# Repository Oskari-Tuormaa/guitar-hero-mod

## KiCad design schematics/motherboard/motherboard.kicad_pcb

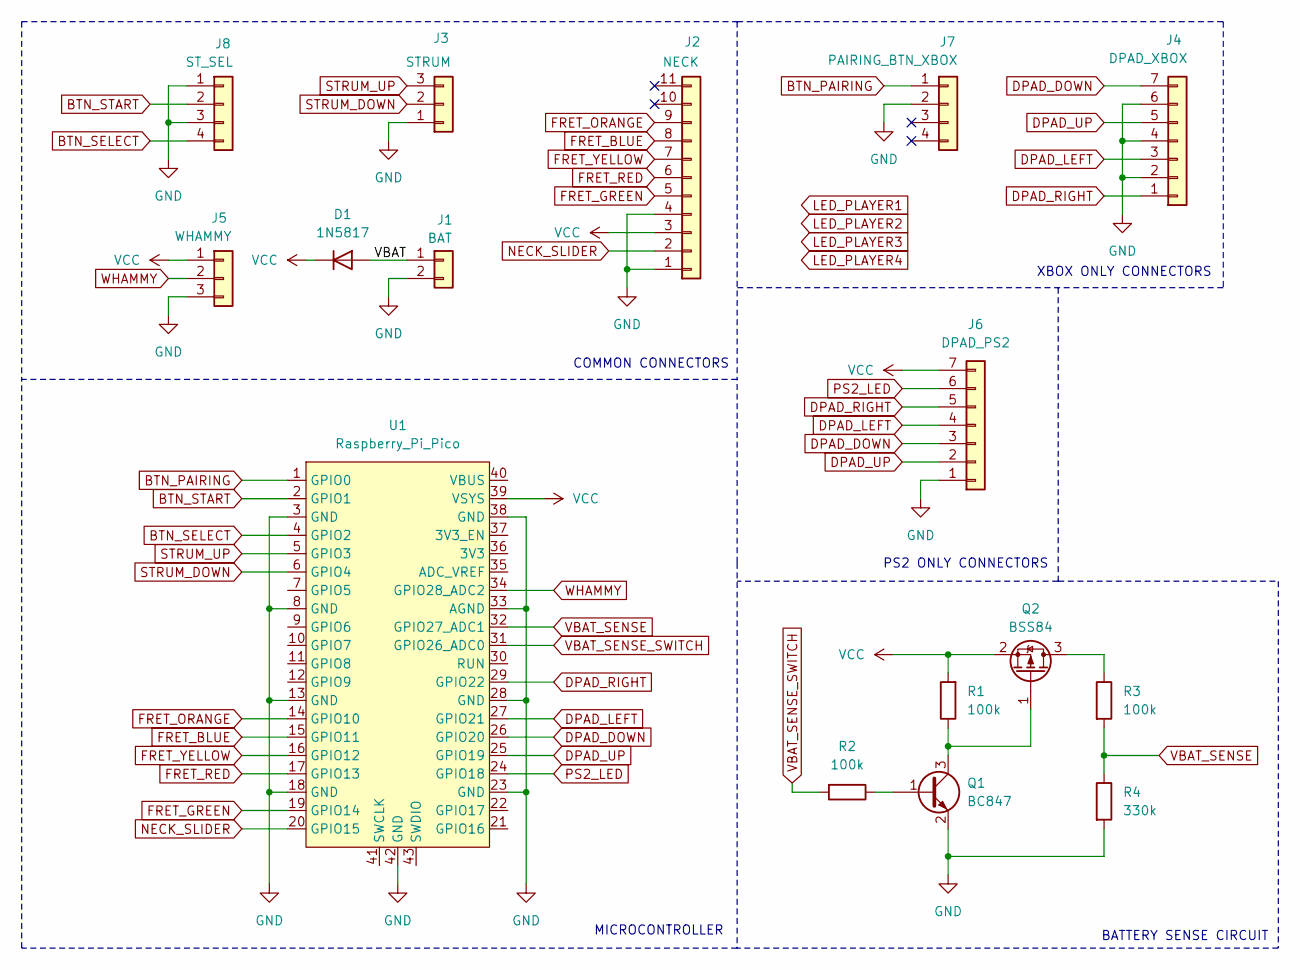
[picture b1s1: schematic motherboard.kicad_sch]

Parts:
D1: 1N5817; D_DO-41_SOD81_P7.62mm_Horizontal
J1: BAT; PinHeader_1x02_P2.00mm_Vertical
J2: NECK; PinHeader_1x11_P2.00mm_Vertical
J3: STRUM; PinHeader_1x03_P2.00mm_Vertical
J4: DPAD_XBOX; PinHeader_1x07_P2.00mm_Vertical
J5: WHAMMY; PinHeader_1x03_P2.00mm_Vertical
J6: DPAD_PS2; PinHeader_1x07_P2.00mm_Vertical
J7: PAIRING_BTN_XBOX; PinHeader_1x04_P2.00mm_Vertical
J8: ST_SEL; PinHeader_1x04_P2.00mm_Vertical
Q1: BC847; SOT-23
Q2: BSS84; SOT-23
R1, R2, R3: 100k; R_1206_3216Metric
R4: 330k; R_1206_3216Metric
U1: Raspberry_Pi_Pico

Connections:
/VBAT: D1.2 (A), J1.1
BTN_PAIRING: J7.1, U1.1 (GPIO0)
BTN_SELECT: J8.4, U1.4 (GPIO2)
BTN_START: J8.2, U1.2 (GPIO1)
DPAD_DOWN: J4.7, J6.3, U1.26 (GPIO20)
DPAD_LEFT: J4.3, J6.4, U1.27 (GPIO21)
DPAD_RIGHT: J4.1, J6.5, U1.29 (GPIO22)
DPAD_UP: J4.5, J6.2, U1.25 (GPIO19)
FRET_BLUE: J2.8, U1.15 (GPIO11)
FRET_GREEN: J2.5, U1.19 (GPIO14)
FRET_ORANGE: J2.9, U1.14 (GPIO10)
FRET_RED: J2.6, U1.17 (GPIO13)
FRET_YELLOW: J2.7, U1.16 (GPIO12)
GND: J1.2, J2.1, J2.4, J3.1, J4.2, J4.4, J4.6, J5.3, J6.1, J7.2, J8.1, J8.3, Q1.2 (E), R4.2, U1.3 (GND), U1.8 (GND), U1.13 (GND), U1.18 (GND), U1.23 (GND), U1.28 (GND), U1.33 (AGND), U1.38 (GND), U1.42 (GND)
NECK_SLIDER: J2.2, U1.20 (GPIO15)
unnamed: Q1.1 (B), R2.1
unnamed: Q1.3 (C), Q2.1 (G), R1.1
unnamed: Q2.3 (D), R3.1
PS2_LED: J6.6, U1.24 (GPIO18)
STRUM_DOWN: J3.2, U1.6 (GPIO4)
STRUM_UP: J3.3, U1.5 (GPIO3)
VBAT_SENSE: R3.2, R4.1, U1.32 (GPIO27_ADC1)
VBAT_SENSE_SWITCH: R2.2, U1.31 (GPIO26_ADC0)
VCC: D1.1 (K), J2.3, J5.1, J6.7, Q2.2 (S), R1.2, U1.39 (VSYS)
WHAMMY: J5.2, U1.34 (GPIO28_ADC2)

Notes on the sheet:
BATTERY SENSE CIRCUIT
COMMON CONNECTORS
MICROCONTROLLER
XBOX ONLY CONNECTORS
PS2 ONLY CONNECTORS

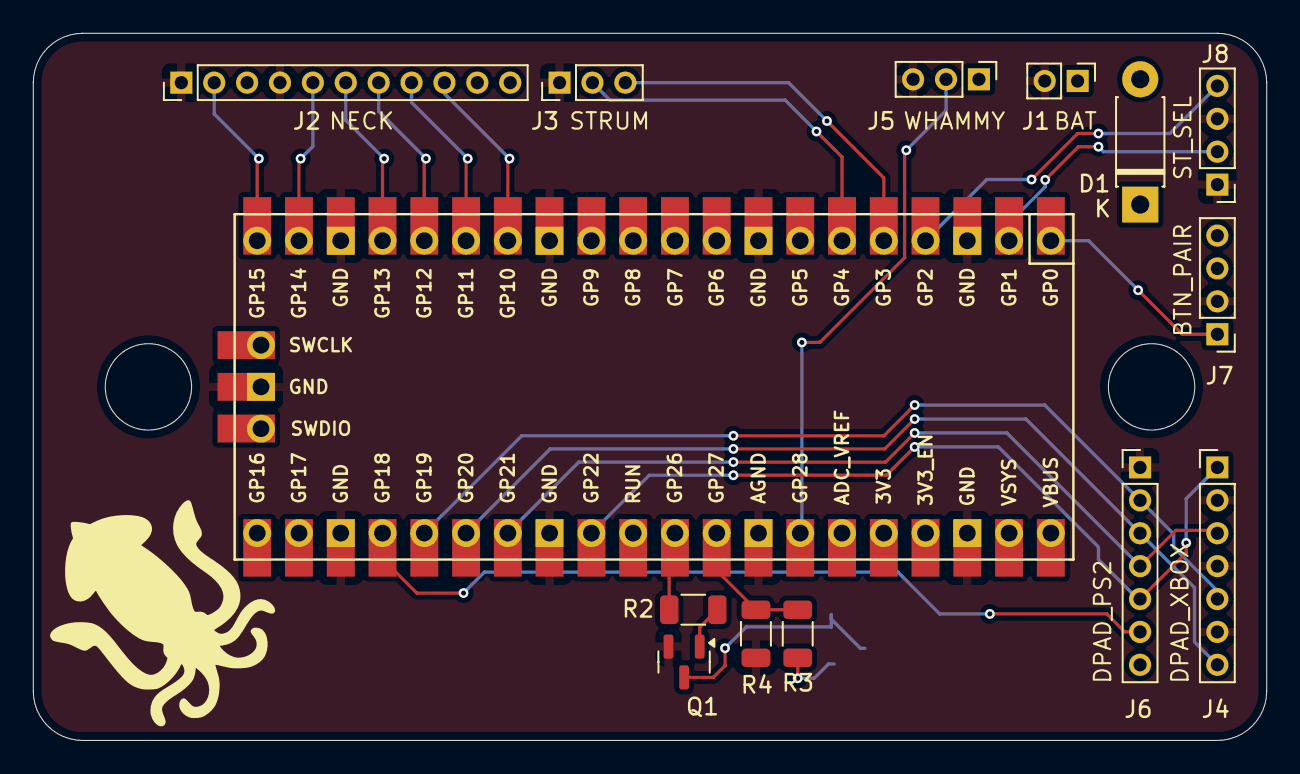
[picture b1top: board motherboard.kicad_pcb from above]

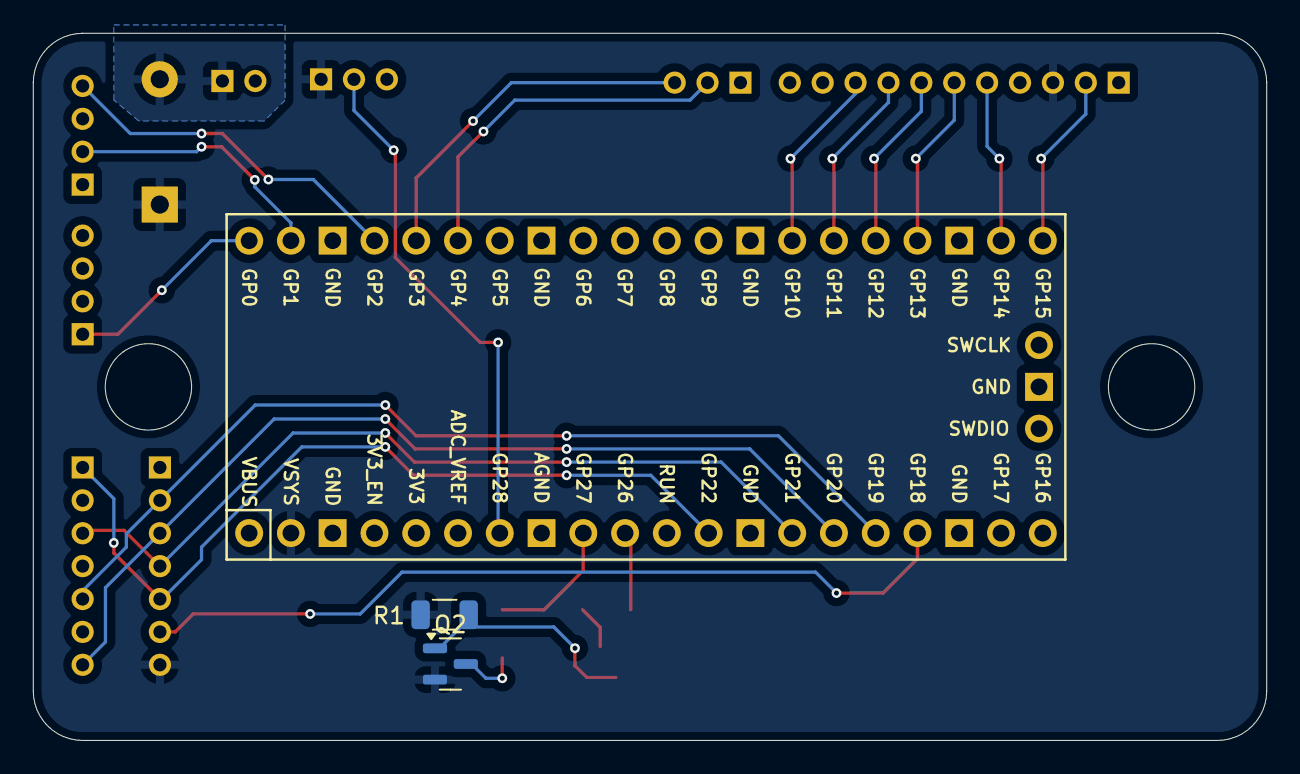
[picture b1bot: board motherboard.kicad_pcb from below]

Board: 2 copper layers, 75.0 x 43.0 mm, 16 parts (2 on the bottom side), 25 nets.

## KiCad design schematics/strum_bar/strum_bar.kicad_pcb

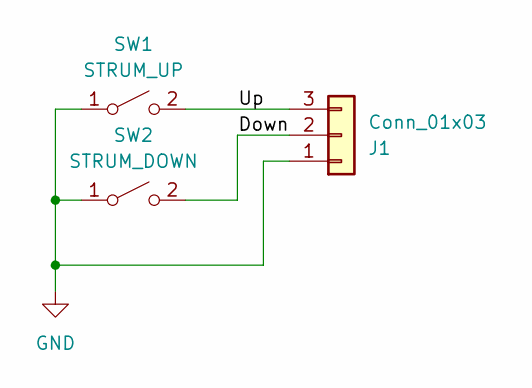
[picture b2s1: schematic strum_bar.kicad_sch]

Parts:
J1: Conn_01x03; PinHeader_1x03_P2.00mm_Vertical
SW1: STRUM_UP; MX_PCB
SW2: STRUM_DOWN; MX_PCB

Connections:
/Down: J1.2, SW2.2 (B)
/Up: J1.3, SW1.2 (B)
GND: J1.1, SW1.1 (A), SW2.1 (A)

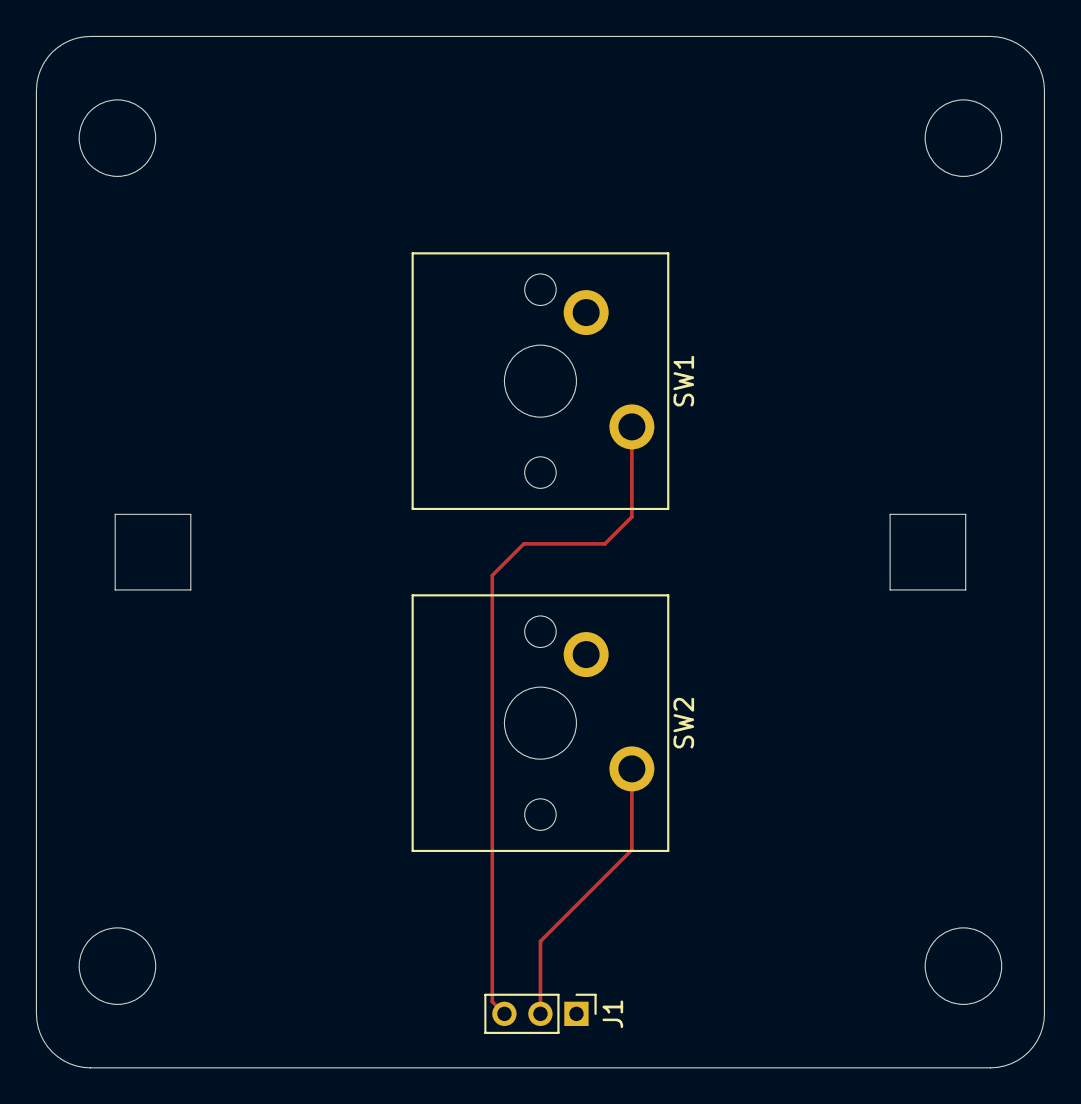
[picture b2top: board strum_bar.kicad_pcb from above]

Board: 2 copper layers, 56.0 x 57.3 mm, 3 parts (0 on the bottom side), 3 nets.

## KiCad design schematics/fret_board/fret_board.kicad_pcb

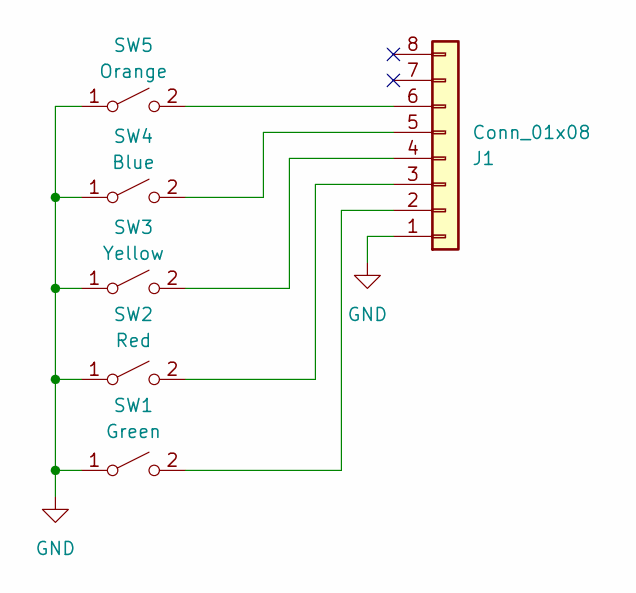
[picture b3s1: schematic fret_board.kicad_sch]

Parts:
J1: Conn_01x08; PinHeader_1x08_P2.00mm_Vertical
SW1: Green; Choc_V1_sunken
SW2: Red; Choc_V1_sunken
SW3: Yellow; Choc_V1_sunken
SW4: Blue; Choc_V1_sunken
SW5: Orange; Choc_V1_sunken

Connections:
GND: J1.1, SW1.1 (A), SW2.1 (A), SW3.1 (A), SW4.1 (A), SW5.1 (A)
unnamed: J1.2, SW1.2 (B)
unnamed: J1.3, SW2.2 (B)
unnamed: J1.4, SW3.2 (B)
unnamed: J1.5, SW4.2 (B)
unnamed: J1.6, SW5.2 (B)

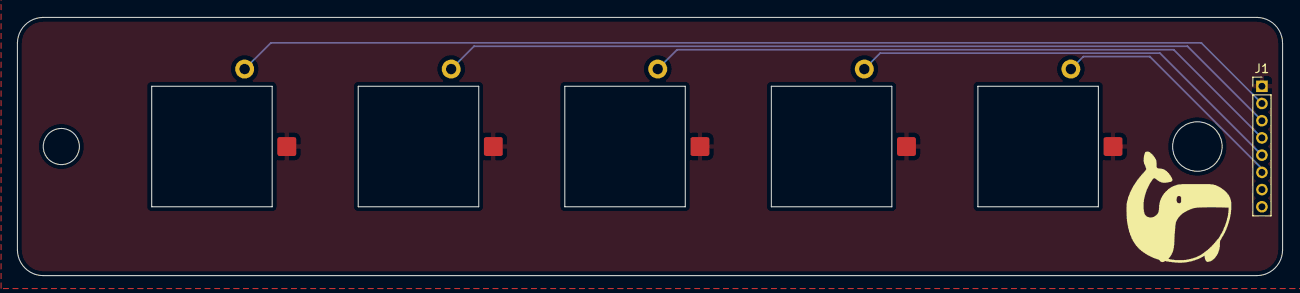
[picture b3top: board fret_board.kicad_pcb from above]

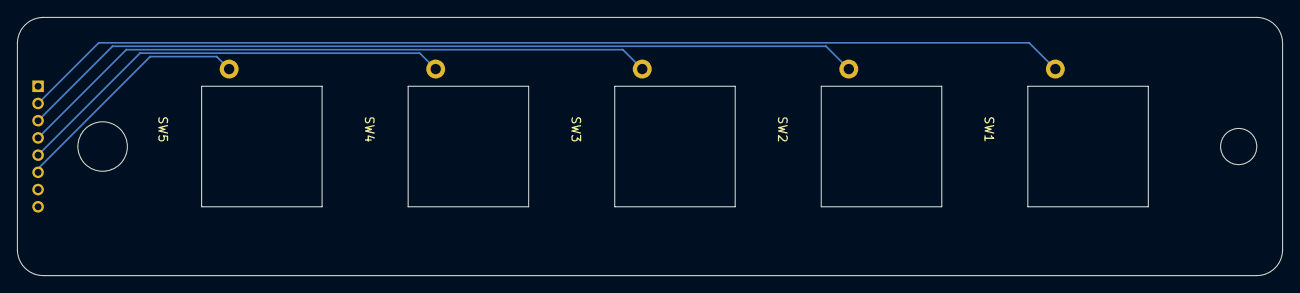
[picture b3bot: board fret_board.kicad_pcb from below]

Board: 2 copper layers, 146.9 x 29.9 mm, 6 parts (5 on the bottom side), 6 nets.

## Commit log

2024-08-17 Add pico-sdk as submodule
2024-08-18 Ignore cache and build dirs
2024-08-18 Add clang-format and clang-tidy files
2024-08-18 Add bluetooth_hid_test
2024-08-19 Updates to bluetooth_hid_test
2024-08-19 Add gamepad_hid_test
2024-08-19 Add guitar_hid_test
2024-08-20 Add world-tour-guitar-HID-descriptor.md
2024-08-20 Fix indentation
2024-08-20 Move descriptor to hid_stuff.h and change descriptor to match GH guitar
2024-08-20 Remove compile_commands.json
2024-08-22 Add padding to gamepad HID descriptor
2024-08-22 Add flash_erase.sh script
2024-08-22 Update .clang-format
2024-08-22 Updates to HID descriptor and a bunch of other stuff
2024-08-28 Move pico-sdk to 3rdparty directory
2024-08-28 Add scottokeebs as subdirectory
2024-08-28 Add initial fret_board pcb files
2024-08-28 Added schematic and PCB design to fret_board
2024-08-28 Flip fret_board connector
2024-08-28 Add strum_bar kicad file
2024-08-28 Add initial empty motherboard schematic project
2024-08-29 Fix awkward ground plane
2024-09-02 Create custom sunken Choc V1 footprint
2024-09-02 Use sunken choc V1 footprint for fretboard
2024-09-02 Move sunken choc pads closer
2024-09-06 Update fret_board, motherboard and strum_bar schematics
2024-09-06 Add fret_button_read_test
2024-09-08 Add more KiCAD stuff to .gitignore
2024-09-08 Add battery sensing circuit and reverse polarity protection diode
2024-09-09 Ignore kicad Gerber output
2024-09-09 Add silkscreen graphics to each schematic
2024-09-14 Add initial version of main_project
2024-09-17 Split HID report into packed and non-packed versions
2024-09-22 A shitton of changes... idk
2024-09-22 More shit
2024-10-03 Working example
2024-11-30 Add FreeRTOS Kernel submodule
2024-11-30 Update to new nvim-workspace way of doing things
2024-12-01 Add simpler version of main project... might complicate it later
2024-12-01 Replace : with <cmd> in workspace
2024-12-02 We're in business
2024-12-02 Change to C++20
2025-04-07 Shit seems to work... sorta
2025-04-10 Split demo into multiple files
2025-04-10 Update Q2 to proper footprint and fix wrong R3/R4 silkscreen
2025-04-10 Update clang-format
